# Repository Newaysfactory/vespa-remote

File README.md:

# vespa-remote
Vespa remote project - a microcontroller based circuit to trigger a gate remote using brake light signal on my Piaggio Vespa
See related youtube video https://youtu.be/zYhpTBYlj2o

## Repo content
 - Electronics - Contains the electronic hardware design (schematics and PCB) created with the free software KiCAD 8.0. Components part numbers are in the spreadsheet BOM_VespaRemoteControl.kicad_pcb.xls 
 - sw - Contains the sw project in MPLAB X IDE v6.25
 - mechanical - Contains the enclosure design in Rhinoceros 8 format. Standard STEP files are available under mechanical\fabrication\

Enjoy

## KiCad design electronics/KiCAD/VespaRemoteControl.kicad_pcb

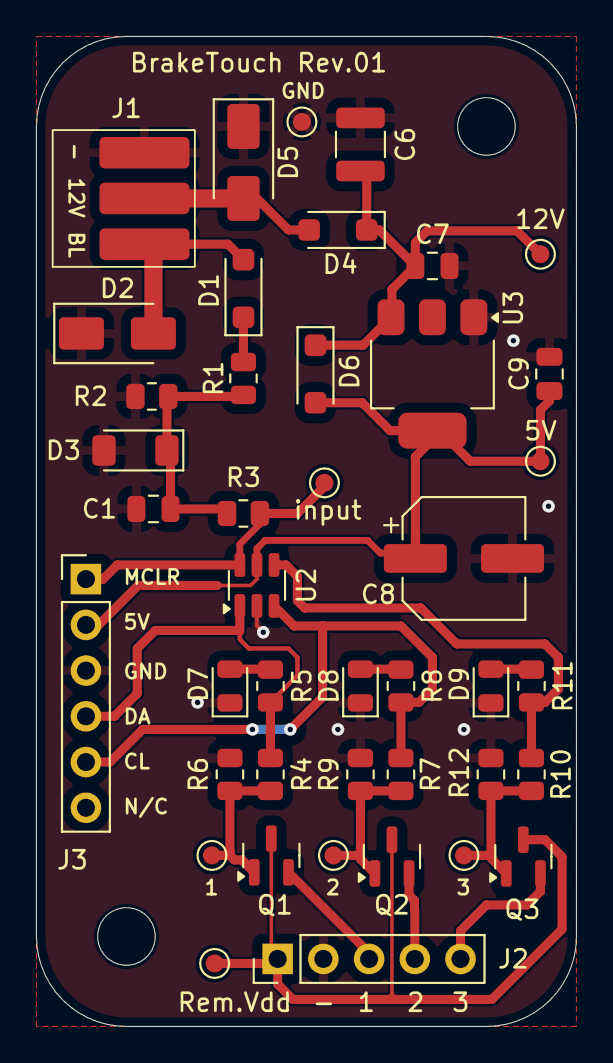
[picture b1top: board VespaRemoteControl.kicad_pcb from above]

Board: 2 copper layers, 30.0 x 55.0 mm, 44 parts (0 on the bottom side), 21 nets.

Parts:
C1: 330nF; C_0805_2012Metric
C6: 10uF 100V; C_1210_3225Metric
C7, C9: 100nF100V; C_0805_2012Metric
C8: 100uF; CP_Elec_6.3x7.7
D1, D4, D6: 1n4007; D_SOD-123FL
D2, D5: SMAJ30CA; D_SMA
D3: 4.7V; D_MiniMELF
D7, D8, D9: LED red; LED_0805_2012Metric
H1, H2: MountingHole; MountingHole_3.2mm_M3
J1: Inputs; SolderWirePad_1x03_SMD_5x2mm
J2: Conn_01x05; PinHeader_1x05_P2.54mm_Vertical
J3: Conn_PIC_ICSP_ICD; PinHeader_1x06_P2.54mm_Vertical
Q1, Q2, Q3: BC817; SOT-23
R1, R5, R8, R11: 1,5k; R_0805_2012Metric
R2: 47k; R_0805_2012Metric
R3, R4, R7, R10: 10k; R_0805_2012Metric
R6, R9, R12: 100k; R_0805_2012Metric
TP1, TP3, TP4, TP5, TP6, TP7, TP8, TP9: TestPoint; My-TestPoint_Pad_D1.0mm
U2: PIC10F222; SOT-23-6
U3: TLV1117-50; SOT-223-3_TabPin2

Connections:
+5V: C8.1, C9.1, D6.2 (A), J3.2 (VDD), TP4.1, U2.5 (VDD), U3.2 (VO)
+12V: C6.1, C7.1, D4.1 (K), D6.1 (K), TP1.1, U3.3 (VI)
/GP0: J3.4 (PGD/ICSPDAT), R4.1, R5.1, U2.1 (GP0)
/GP1: J3.5 (PGC/ICSPCLK), R7.1, R8.1, U2.3 (GP1)
/GP2: R10.1, R11.1, U2.4 (GP2)
/Power In: D4.2 (A), D5.2 (A2), J1.2
/RemoteCh1: J2.3, Q1.2 (E)
/RemoteCh2: J2.4, Q2.2 (E)
/RemoteCh3: J2.5, Q3.2 (E)
/RemoteVdd: J2.1, Q1.3 (C), Q2.3 (C), Q3.3 (C), TP5.1
/brake light_input: D1.2 (A), D2.2 (A2), J1.1
/signal_clean: C1.1, D3.1 (K), R1.1, R2.1, R3.2
GND: C1.2, C6.2, C7.2, C8.2, C9.2, D2.1 (A1), D3.2 (A), D5.1 (A1), D7.1 (K), D8.1 (K), D9.1 (K), J1.3, J2.2, J3.3 (VSS), R2.2, R6.1, R9.1, R12.1, TP9.1, U2.2 (VSS), U3.1 (GND)
MCLR: J3.1 (~MCLR/VPP), R3.1, TP3.1, U2.6 (GP3)
unnamed: D1.1 (K), R1.2
unnamed: D7.2 (A), R5.2
unnamed: D8.2 (A), R8.2
unnamed: D9.2 (A), R11.2
unnamed: Q1.1 (B), R4.2, R6.2, TP6.1
unnamed: Q2.1 (B), R7.2, R9.2, TP7.1
unnamed: Q3.1 (B), R10.2, R12.2, TP8.1

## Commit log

2025-09-04 Adding all files
2025-09-04 Fixing material error
2025-09-04 Adding bill of materials
